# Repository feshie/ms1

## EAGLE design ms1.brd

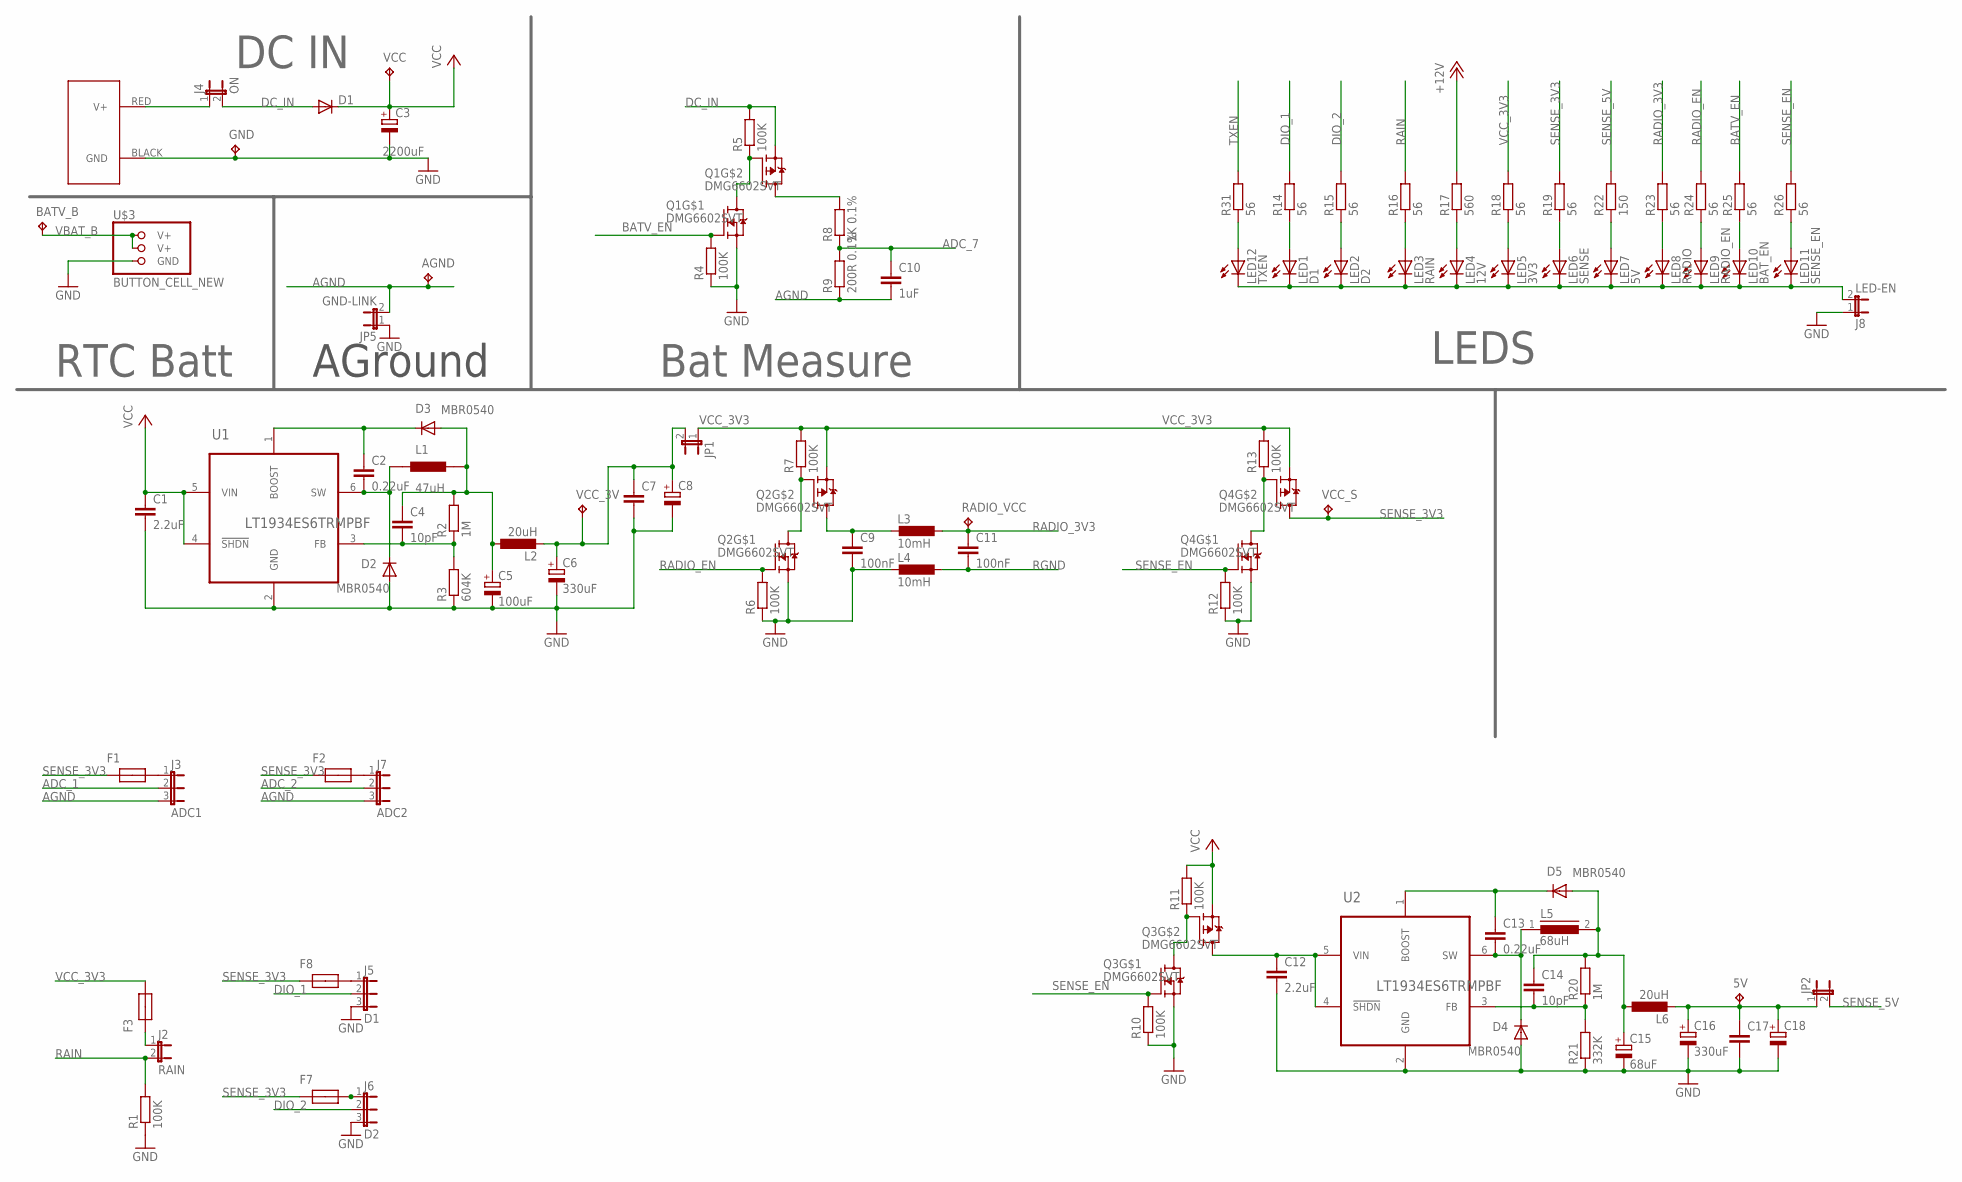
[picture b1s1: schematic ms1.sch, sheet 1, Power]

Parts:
5V: 5V B; B2,54
AGND: TPB2,54; B2,54
BATV_B: 5V B; B2,54
C1, C12: 2.2uF; C0805
C2, C13: 0.22uF; C0805
C3: 2200uF; E5-13
C4, C14: 10pF; C0805
C5: 100uF; PANASONIC_E
C6, C16: 330uF; E5-8,5
C7, C17: C-EUC0805; C0805
C8, C18: CPOL-EUB/3528-21R; B/3528-21R
C9, C11: 100nF; C0805
C10: 1uF; C0805
C15: 68uF; PANASONIC_E
D1: DIODE-SMB; SMB
D2, D3, D4, D5: MBR0540; SOD123
F1, F2, F3, F7, F8: MCF0805; 0805
GND: 5V B; B2,54
J1: POWERPOLE_POWER25A; POWERPOLE_PAIR_25A
J2: RAIN; 2-MOLEX
J3: ADC1; 3-MOLEX
J4: ON; 2-MOLEX
J5: D1; 3-MOLEX
J6: D2; 3-MOLEX
J7: ADC2; 3-MOLEX
J8: LED-EN; 2-MOLEX
JP1, JP2: JUMPER-2SMD-NO; SJ_2S-NO
JP5: GND-LINK; JP1
L1: 47uH; 1048
L2, L6: 20uH; 6000-XXXX-RC
L3, L4: 10mH; L3230M
L5: 68uH; DR127
LED1: D1; CHIP-LED0805
LED2: D2; CHIP-LED0805
LED3: RAIN; CHIP-LED0805
LED4: 12V; CHIP-LED0805
LED5: 3V3; CHIP-LED0805
LED6: SENSE; CHIP-LED0805
LED7: 5V; CHIP-LED0805
LED8: RADIO; CHIP-LED0805
LED9: RADIO_EN; CHIP-LED0805
LED10: BAT_EN; CHIP-LED0805
LED11: SENSE_EN; CHIP-LED0805
LED12: TXEN; CHIP-LED0805
Q1, Q2, Q3, Q4: DMG6602SVT; TSOT26
R1, R4, R5, R6, R7, R10, R11, R12, R13: 100K; R0805
R2, R20: 1M; R0805
R3: 604K; R0805
R8: 1K 0.1%; R0805
R9: 200R 0.1%; R0805
R14, R15, R16, R18, R19, R23, R24, R25, R26, R31: 56; R0805
R17: 560; R0805
R21: 332K; R0805
R22: 150; R0805
RADIO_VCC: TPB2,54; B2,54
U1, U2: LT1934ES6TRMPBF; SOT95P280X100-6N
U$3: BUTTON_CELL_NEW; CR2016
VCC: TPB2,54; B2,54
VCC_3V: TPB2,54; B2,54
VCC_S: TPB2,54; B2,54

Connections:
ADC_1: J3.2; also elsewhere on the board
ADC_2: J7.2; also elsewhere on the board
ADC_7: C10.1, R8.1, R9.2; also elsewhere on the board
AGND: AGND.TP, C10.2, J3.3, J7.3, JP5.2, R9.1; also elsewhere on the board
BATV_EN: Q1.P$1 (G), R4.2, R25.2; also elsewhere on the board
DC_IN: D1.A, J4.2, Q1.P$2 (S), R5.2
DIO_1: J5.2, R14.2; also elsewhere on the board
DIO_2: J6.2, R15.2; also elsewhere on the board
GND: C1.2, C3.-, C5.-, C6.-, C7.2, C8.-, C9.2, C12.2, C15.-, C16.-, C17.2, C18.-, D2.A, D4.A, GND.TP, J1.BLACK (GND), J5.3, J6.3, J8.1, JP5.1, L4.2, Q1.P$5 (S), Q2.P$5 (S), Q3.P$5 (S), Q4.P$5 (S), R1.1, R3.1, R4.1, R6.1, R10.1, R12.1, R21.1, U1.2 (GND), U2.2 (GND), U$3.GND; also elsewhere on the board
LGND: J8.2, LED1.C, LED2.C, LED3.C, LED4.C, LED5.C, LED6.C, LED7.C, LED8.C, LED9.C, LED10.C, LED11.C, LED12.C
unnamed: J1.RED (V+), J4.1
unnamed: LED4.A, R17.1
unnamed: C13.2, D4.C, L5.1, U2.6 (SW)
unnamed: C13.1, D5.C, U2.1 (BOOST)
unnamed: C14.2, R20.1, R21.2, U2.3 (FB)
unnamed: C14.1, C15.+, D5.A, L5.2, L6.1, R20.2
unnamed: Q2.P$3 (G), Q2.P$6 (D), R7.1
unnamed: Q1.P$3 (G), Q1.P$6 (D), R5.1
unnamed: C6.+, C7.1, C8.+, JP1.2, L2.2, VCC_3V.TP
unnamed: 5V.TP, C16.+, C17.1, C18.+, JP2.1, L6.2
unnamed: LED9.A, R24.1
unnamed: LED3.A, R16.1
unnamed: F1.2, J3.1
unnamed: F2.2, J7.1
unnamed: LED2.A, R15.1
unnamed: F7.2, J6.1
unnamed: F8.2, J5.1
unnamed: LED1.A, R14.1
unnamed: C9.1, L3.2, Q2.P$4 (D)
unnamed: Q3.P$3 (G), Q3.P$6 (D), R11.1
unnamed: F3.1, J2.1
unnamed: LED12.A, R31.1
unnamed: LED10.A, R25.1
unnamed: LED11.A, R26.1
unnamed: Q4.P$3 (G), Q4.P$6 (D), R13.1
unnamed: C2.2, D2.C, L1.1, U1.6 (SW)
unnamed: C4.1, C5.+, D3.A, L1.2, L2.1, R2.2
unnamed: LED8.A, R23.1
unnamed: LED7.A, R22.1
unnamed: LED6.A, R19.1
unnamed: LED5.A, R18.1
unnamed: C2.1, D3.C, U1.1 (BOOST)
unnamed: C4.2, R2.1, R3.2, U1.3 (FB)
RADIO_3V3: C11.1, L3.1, R23.2, RADIO_VCC.TP; also elsewhere on the board
RADIO_EN: Q2.P$1 (G), R6.2, R24.2; also elsewhere on the board
RAIN: J2.2, R1.2, R16.2; also elsewhere on the board
RGND: C11.2, L4.1; also elsewhere on the board
SENSE_3V3: F1.1, F2.1, F7.1, F8.1, Q4.P$4 (D), R19.2, VCC_S.TP; also elsewhere on the board
SENSE_5V: JP2.2, R22.2; also elsewhere on the board
SENSE_EN: Q3.P$1 (G), Q4.P$1 (G), R10.2, R12.2, R26.2; also elsewhere on the board
TXEN: R31.2; also elsewhere on the board
VBAT_B: BATV_B.TP, U$3.V+@1 (V+), U$3.V+@2 (V+); also elsewhere on the board
VCC: C1.1, C3.+, D1.C, Q3.P$2 (S), R11.2, R17.2, U1.4 (!SHDN), U1.5 (VIN), VCC.TP
VCC_3V3: F3.2, JP1.1, Q2.P$2 (S), Q4.P$2 (S), R7.2, R13.2, R18.2; also elsewhere on the board
VCC_HP2_SW: C12.1, Q3.P$4 (D), U2.4 (!SHDN), U2.5 (VIN)
VCC_HP2_SW1: Q1.P$4 (D), R8.2

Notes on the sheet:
LEDS
DC IN
Bat Measure
RTC Batt
AGround

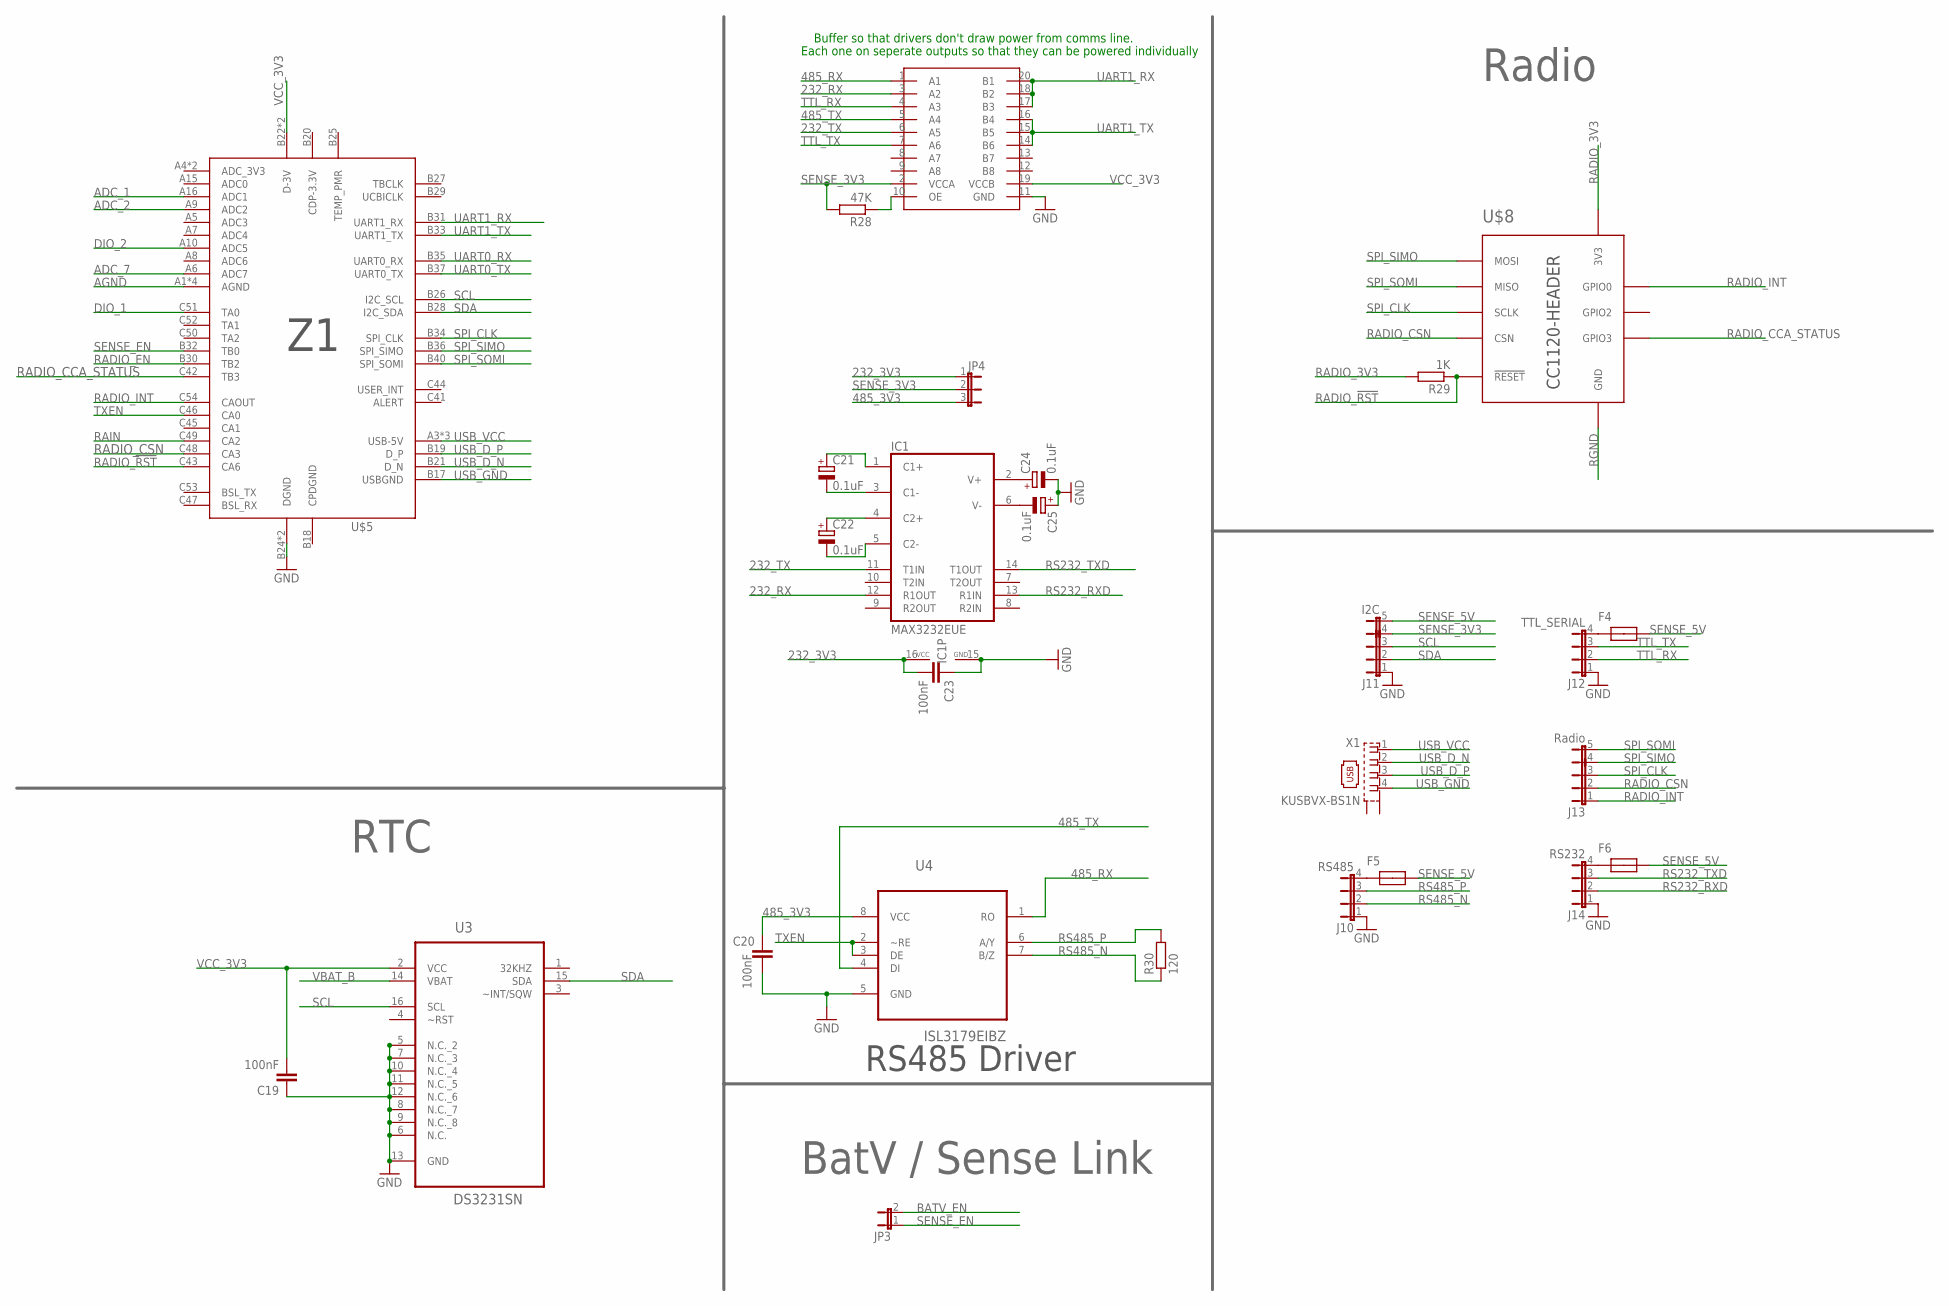
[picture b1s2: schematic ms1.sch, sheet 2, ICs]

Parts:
C19, C20, C23: 100nF; C0805
C21, C22, C24, C25: 0.1uF; A/3216-18W
F4, F5, F6: MCF0805; 0805
IC1: MAX3232EUE; TSSOP16
J10: RS485; 4-MOLEX
J11: I2C; 5-MOLEX
J12: TTL_SERIAL; 4-MOLEX
J13: Radio; 5-MOLEX
J14: RS232; 4-MOLEX
JP3: JUMPER-2SMD-NC; SJ_2S
JP4: JP2E; JP2
R28: 47K; R0805
R29: 1K; R0805
R30: 120; R0805
U3: DS3231SN; SOIC127P1032X265-16N
U4: ISL3179EIBZ; SOIC127P600X175-8N
U$5: Z1
U$6: TXS0108E; TSSOP20
U$8: CC1120-HEADER-SMT; CC1120-HEADERS-SMT
X1: KUSBVX-BS1N

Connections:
232_3V3: C23.2, IC1.16 (VCC), JP4.1
232_RX: IC1.12 (R1OUT), U$6.3 (A2)
232_TX: IC1.11 (T1IN), U$6.6 (A5)
485_3V3: C20.1, JP4.3, U4.8 (VCC)
485_RX: U4.1 (RO), U$6.1 (A1)
485_TX: U4.4 (DI), U$6.5 (A4)
ADC_1: U$5.A16 (ADC1); also elsewhere on the board
ADC_2: U$5.A9 (ADC2); also elsewhere on the board
ADC_3V3: U$5.A4 (ADC_3V3), U$5.A14 (ADC_3V3)
ADC_7: U$5.A6 (ADC7); also elsewhere on the board
AGND: U$5.A1 (AGND), U$5.A2 (AGND), U$5.A11 (AGND), U$5.A12 (AGND); also elsewhere on the board
BATV_EN: JP3.2; also elsewhere on the board
DIO_1: U$5.C51 (TA0); also elsewhere on the board
DIO_2: U$5.A10 (ADC5); also elsewhere on the board
GND: C19.1, C20.2, C23.1, C24.-, C25.+, IC1.15 (GND), J10.1, J11.1, J12.1, J14.1, U3.5 (N.C._2), U3.6 (N.C.), U3.7 (N.C._3), U3.8 (N.C._7), U3.9 (N.C._8), U3.10 (N.C._4), U3.11 (N.C._5), U3.12 (N.C._6), U3.13 (GND), U4.5 (GND), U$5.B24 (DGND), U$5.C39 (DGND), U$6.11 (GND); also elsewhere on the board
unnamed: R28.1, U$6.10 (OE)
unnamed: F5.1, J10.4
unnamed: F4.1, J12.4
unnamed: F6.1, J14.4
unnamed: C22.-, IC1.5 (C2-)
unnamed: C22.+, IC1.4 (C2+)
unnamed: C21.-, IC1.3 (C1-)
unnamed: C21.+, IC1.1 (C1+)
unnamed: C24.+, IC1.2 (V+)
unnamed: C25.-, IC1.6 (V-)
RADIO_3V3: R29.2, U$8.3V3-1 (3V3), U$8.3V3-2 (3V3); also elsewhere on the board
RADIO_!RST: R29.1, U$5.C43 (CA6), U$8.RESET (!RESET)
RADIO_CCA_STATUS: U$5.C42 (TB3), U$8.GPIO3
RADIO_CSN: J13.2, U$5.C48 (CA3), U$8.CSN
RADIO_EN: U$5.B30 (TB2); also elsewhere on the board
RADIO_INT: J13.1, U$5.C54 (CAOUT), U$8.GPIO0
RAIN: U$5.C49 (CA2); also elsewhere on the board
RGND: U$8.GND, U$8.GND1 (GND), U$8.GND2 (GND); also elsewhere on the board
RS232_RXD: IC1.13 (R1IN), J14.2
RS232_TXD: IC1.14 (T1OUT), J14.3
RS485_N: J10.2, R30.1, U4.7 (B/Z)
RS485_P: J10.3, R30.2, U4.6 (A/Y)
SCL: J11.3, U3.16 (SCL), U$5.B26 (I2C_SCL)
SDA: J11.2, U3.15 (SDA), U$5.B28 (I2C_SDA)
SENSE_3V3: J11.4, JP4.2, R28.2, U$6.2 (VCCA); also elsewhere on the board
SENSE_5V: F4.2, F5.2, F6.2, J11.5 (6); also elsewhere on the board
SENSE_EN: JP3.1, U$5.B32 (TB0); also elsewhere on the board
SPI_CLK: J13.3, U$5.B34 (SPI_CLK), U$8.SCLK
SPI_SIMO: J13.4, U$5.B36 (SPI_SIMO), U$8.MOSI
SPI_SOMI: J13.5 (6), U$5.B40 (SPI_SOMI), U$8.MISO
TTL_RX: J12.2, U$6.4 (A3)
TTL_TX: J12.3, U$6.7 (A6)
TXEN: U4.2 (~RE), U4.3 (DE), U$5.C46 (CA0); also elsewhere on the board
UART0_RX: U$5.B35 (UART0_RX)
UART0_TX: U$5.B37 (UART0_TX)
UART1_RX: U$5.B31 (UART1_RX), U$6.17 (B3), U$6.18 (B2), U$6.20 (B1)
UART1_TX: U$5.B33 (UART1_TX), U$6.14 (B6), U$6.15 (B5), U$6.16 (B4)
USB_D_N: U$5.B21 (D_N), X1.2
USB_D_P: U$5.B19 (D_P), X1.3
USB_GND: U$5.B17 (USBGND), X1.4
USB_VCC: U$5.A3 (USB-5V), U$5.A13 (USB-5V), U$5.B23 (USB-5V), X1.1
VBAT_B: U3.14 (VBAT); also elsewhere on the board
VCC_3V3: C19.2, U3.2 (VCC), U$5.B22 (D-3V), U$5.C40 (D-3V), U$6.19 (VCCB); also elsewhere on the board

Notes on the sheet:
RTC
Radio
BatV / Sense Link
RS485 Driver
Buffer so that drivers don't draw power from comms line.
Each one on seperate outputs so that they can be powered individually

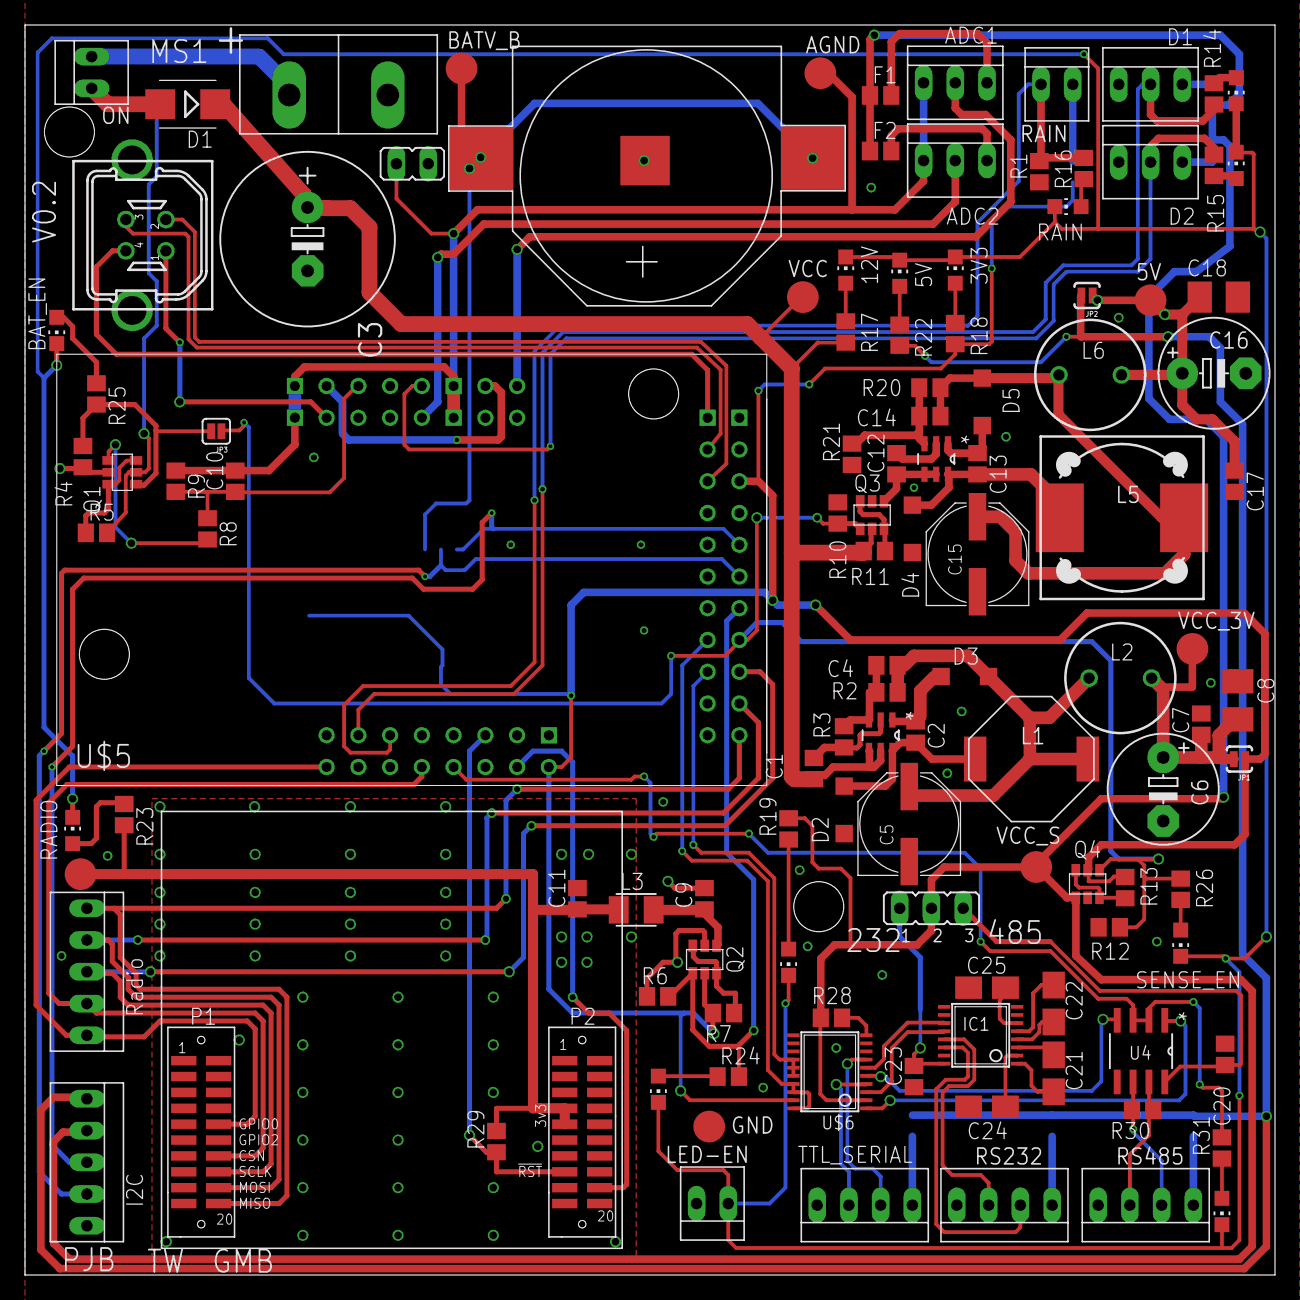
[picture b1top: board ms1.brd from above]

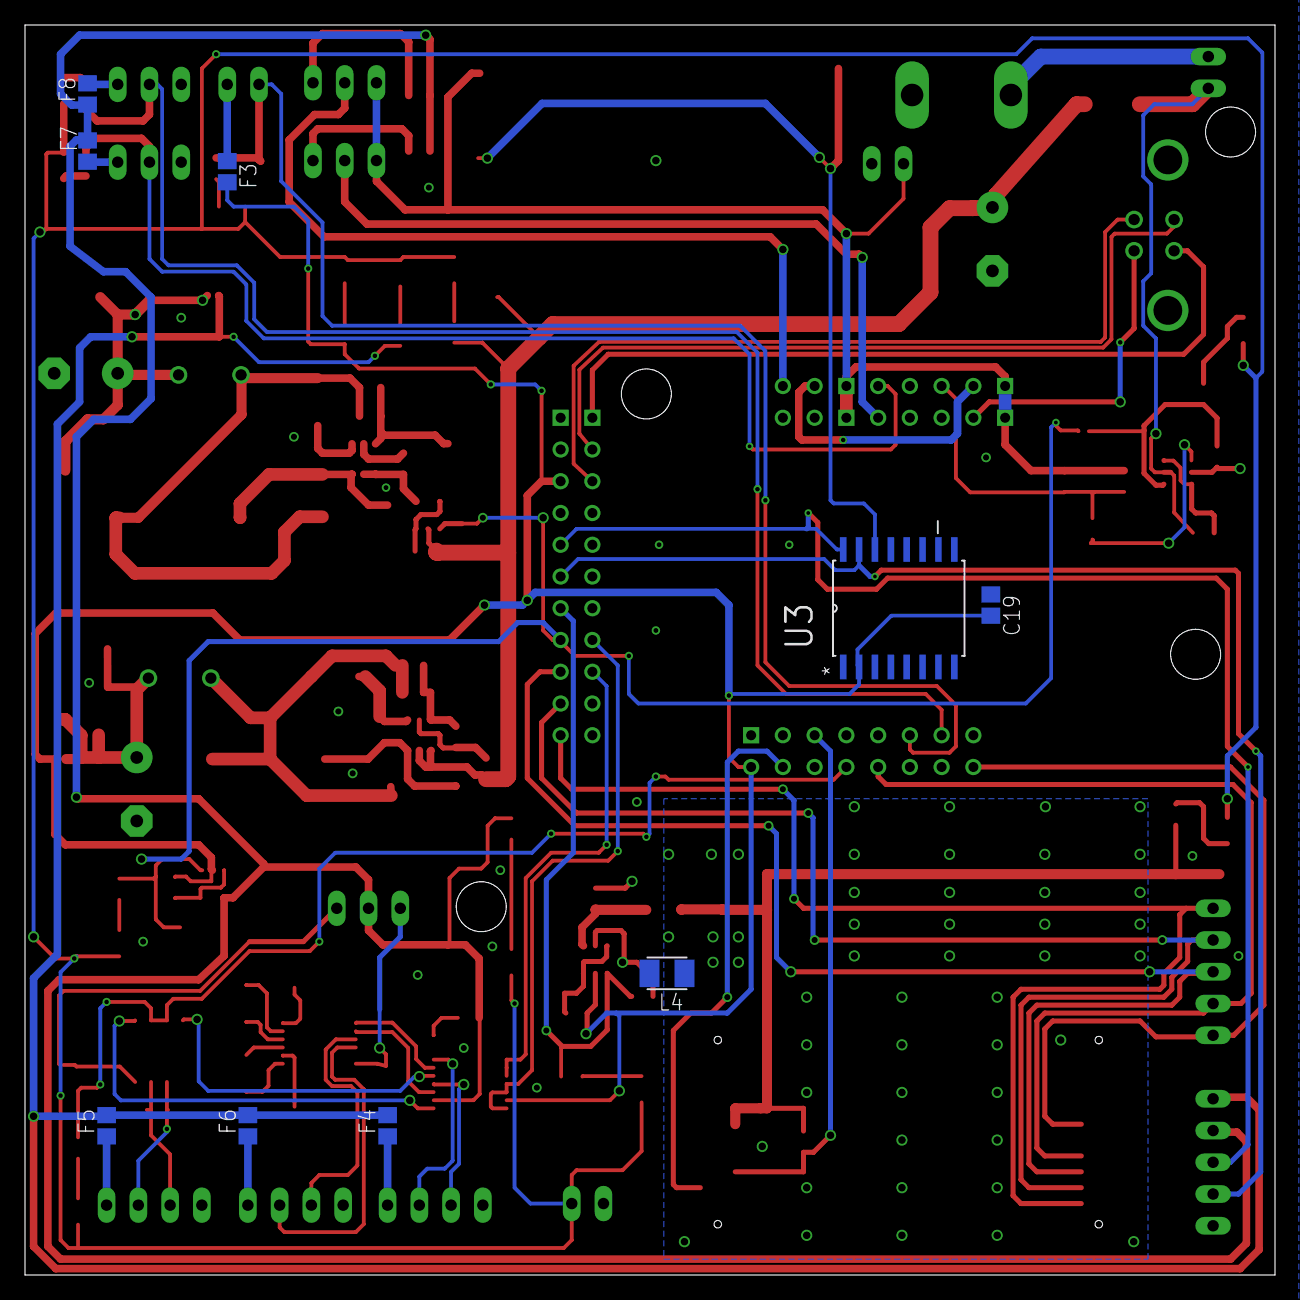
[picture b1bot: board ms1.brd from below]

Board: 2 copper layers, 100.0 x 100.0 mm, 126 parts (9 on the bottom side), 94 nets.

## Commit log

2014-05-02 First bits of design for node
2014-05-02 rtc added
2014-05-06 Added waspmote part & cc1120 added vbat measure added radio switched power started to add connectors
2014-05-09 started to connect things up
2014-05-09 added headers for I/O tidying up schematic added SPI to wasp
2014-05-09 finsihed boxing fixed a couple of ERC errors reduced to one page now smd input protection diode
2014-05-09 renumbered
2014-05-10 filtering for radio vcc inductor removed for AGND as it's on Z1 ERC checking performed
2014-05-10 start of PCB layout
2014-05-12 a little more routing
2014-05-12 power supplies mostly routed
2014-05-13 serial stuff laid out
2014-05-23 added pullup to !RESET on CC1120
2014-05-26 added reset link from cc1120 to msp
2014-05-27 cc1120 wiring matches test harness
2014-05-31 now has cca pin
2014-06-02 routed GPIO3
2014-06-05 now uses dr127 for 5w inductor
2014-06-05 more smoothing to 5v rail
2014-06-08 more smoothing on 3v3 output
2014-06-17 minor routing changes
2014-06-17 more routing - mainly digital signals
2014-06-18 removal of libellium part
2014-06-18 now uses correct serial buffer
2014-06-18 now has: * rain gauge input * 2 digital io * 2 analog io * poly fuses
2014-06-18 now all routed :)
2014-06-19 A couple of small bugfixes
    Moved battery + away from battery negative terminal
    moved clearance issue via
2014-06-19 silk screen worked
2014-06-23 As submitted to hackvana
2014-09-02 fixes #2 now has rs483 termination resistor
2014-09-02 fixes #7 now has gnd link header
2014-09-02 fixes #4 all the same pins on z1 are now linked
2014-09-02 DIO remapped to be TXEN for rs485, new DIO pin not yet selected
2014-09-04 Fixes #1 DIO_2 now on ADC5 which can be used for digital IO, and the hack permenantly routed to rs485 driver
2014-09-29 now with correct values for batv divider
2015-09-25 Added basic block diagram of MS1 design
2015-09-29 Corrections to MS1 block diagram
2016-08-19 Updated block diagram for Gen 2, added exports of gen 2 for Sensys paper

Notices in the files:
parts and their libraries:
SparkFun-Passives: Licensing: Creative Commons ShareAlike 4.0 International - https://creativecommons.org/licenses/by-sa/4.0
